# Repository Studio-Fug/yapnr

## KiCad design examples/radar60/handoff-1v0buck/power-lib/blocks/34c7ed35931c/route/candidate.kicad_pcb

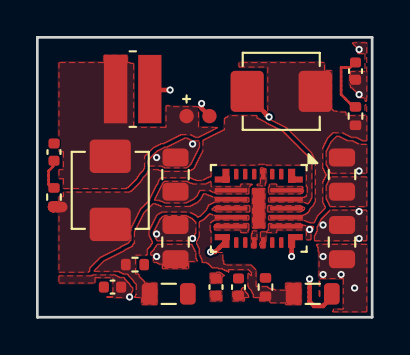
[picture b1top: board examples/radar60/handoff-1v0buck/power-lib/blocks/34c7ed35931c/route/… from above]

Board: 6 copper layers, 18.6 x 15.5 mm, 20 parts (0 on the bottom side), 15 nets.

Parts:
C14, C15, C16, C17: C_0805_2012Metric
C27, C28, C29, C30, C31: C_0402_1005Metric
L1, L2: L_0805_2012Metric
L3, L4: L_Vishay_IHLP-1616
R30, R31, R32, R33: R_0402_1005Metric
R_SH1: Vishay_WFCP0612_1632Metric
TP1: Radar60_KelvinSense_2Pad_P1.27mm
U2: TI_RNF0026C_VQFN-HR-26_4.5x4mm_P0.5mm

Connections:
1V0_BUCK: L3.2, R_SH1.1, TP1.1
1V0_SH: R_SH1.2, TP1.2
1V2_BUCK: L2.2, U2.14
1V8_BUCK: L4.2, U2.21
3V3: L1.2, U2.8
5V_SYS: C14.1, C15.1, C16.1, C17.1, C31.1, U2.9, U2.13, U2.18, U2.22, U2.26
GND: C14.2, C15.2, C16.2, C17.2, C27.2, C28.2, C29.2, C30.2, C31.2, U2.4, U2.11, U2.17, U2.24, U2.27
PMIC_SW_B0: L1.1, R30.1, U2.10
PMIC_SW_B1: L2.1, R31.1, U2.12
PMIC_SW_B2: L3.1, R32.1, U2.25
PMIC_SW_B3: L4.1, R33.1, U2.23
snb0: C27.1, R30.2
snb1: C28.1, R31.2
snb2: C29.1, R32.2
snb3: C30.1, R33.2

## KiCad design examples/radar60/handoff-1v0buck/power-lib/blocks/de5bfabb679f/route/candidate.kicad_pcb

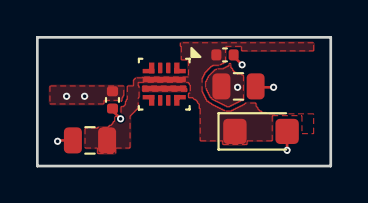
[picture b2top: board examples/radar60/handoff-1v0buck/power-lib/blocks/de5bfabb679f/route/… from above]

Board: 6 copper layers, 16.3 x 7.1 mm, 6 parts (0 on the bottom side), 3 nets.

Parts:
C33, C36: C_0805_2012Metric
C34, C37: C_0402_1005Metric
D3: D_SMF
U5: TI_RPW0010A_VQFN-HR-10_2x2mm_P0.45mm

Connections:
5V_SYS: C36.1, C37.1, U5.6
GND: C33.2, C34.2, C36.2, C37.2, D3.2, U5.8
VIN_5V: C33.1, C34.1, D3.1, U5.5

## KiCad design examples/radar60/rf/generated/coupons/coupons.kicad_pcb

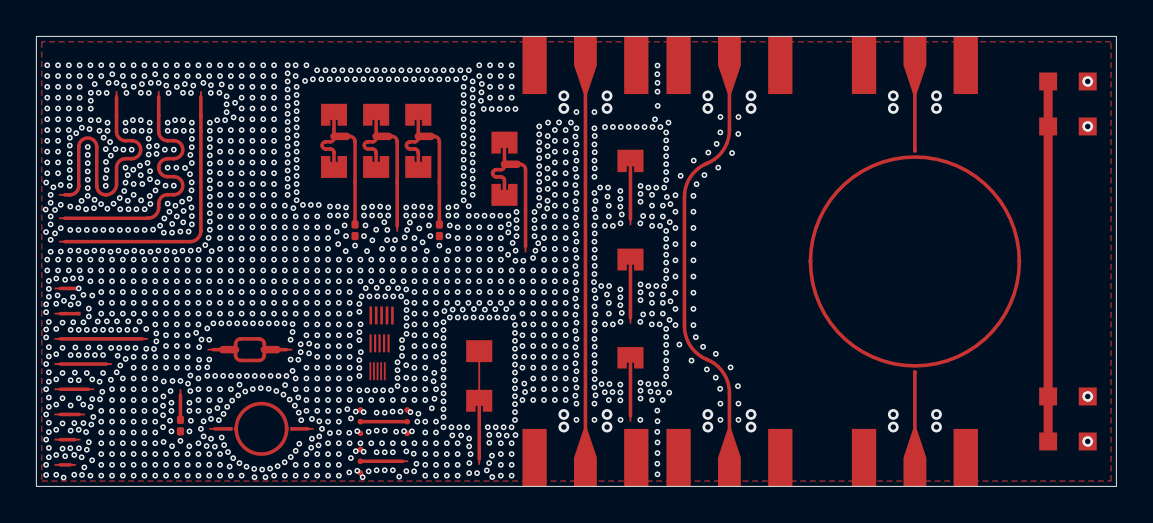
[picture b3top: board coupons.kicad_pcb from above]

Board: 6 copper layers, 60.0 x 25.0 mm, 97 parts (0 on the bottom side), 33 nets.

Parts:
CP0: cp60/0/a; CP_PAD
CP1: cp60/0/b; CP_PAD
CP2: cp60/1/a; CP_PAD
CP3: cp60/1/b; CP_PAD
CP4: cp60/2/a; CP_PAD
CP5: cp60/2/b; CP_PAD
CP6: cp60/3/a; CP_PAD
CP7: cp60/3/b; CP_PAD
CP8: cp60/4/a; CP_PAD
CP9: cp60/4/b; CP_PAD
CP10: cp60/5/a; CP_PAD
CP11: cp60/5/b; CP_PAD
CP12: cp60/open; CP_PAD
CP13: cp60/open/end; CP_PAD
CP14: cp60/short; CP_PAD
CP15: cpz; CP_PAD
CP16: ring60/anchor-1; CP_PAD
CP17: ring60/anchor1; CP_PAD
CP18: ring/a; CP_PAD
CP19: ring/a/end; CP_PAD
CP20: ring/b; CP_PAD
CP21: ring/b/end; CP_PAD
CP22: cpd/a; CP_PAD
CP23: cpd/b; CP_PAD
CP24: cpl1/land18.00; CP_PAD
CP25: cpl1/g18.00-1; CP_PAD
CP26: cpl1/g18.001; CP_PAD
CP27: cpl1/b; CP_PAD
CP28: cpl2/land18.00; CP_PAD
CP29: cpl2/g18.00-1; CP_PAD
CP30: cpl2/g18.001; CP_PAD
CP31: cpl2/land20.60; CP_PAD
CP32: cpl2/g20.60-1; CP_PAD
CP33: cpl2/g20.601; CP_PAD
CP34: cpm/0/0; CP_PAD
CP35: cpm/0/1; CP_PAD
CP36: cpm/0/2; CP_PAD
CP37: cpm/0/3; CP_PAD
CP38: cpm/0/4; CP_PAD
CP39: cpm/1/0; CP_PAD
CP40: cpm/1/1; CP_PAD
CP41: cpm/1/2; CP_PAD
CP42: cpm/1/3; CP_PAD
CP43: cpm/1/4; CP_PAD
CP44: cpm/2/0; CP_PAD
CP45: cpm/2/1; CP_PAD
CP46: cpm/2/2; CP_PAD
CP47: cpm/2/3; CP_PAD
CP48: cpm/2/4; CP_PAD
CP49: cpa/ser/lo; CP_PAD
CP50: cpa/ser/hi; CP_PAD
CP51: cpa/ser/link; CP_PAD
CP52: cpa/ser; CP_PAD
CP53: cpt/TX1/a; CP_PAD
CP54: cpt/TX1/b; CP_PAD
CP55: cpt/TX2/a; CP_PAD
CP56: cpt/TX2/b; CP_PAD
CP57: cpt/TX3/a; CP_PAD
CP58: cpt/TX3/b; CP_PAD
CP59: cpa/cell/0/0; CP_PAD
CP60: cpa/cell/0/1; CP_PAD
CP61: cpa/cell/1/0; CP_PAD
CP62: cpa/cell/1/1; CP_PAD
CP63: cpa/cell; CP_PAD
CP64: cpa/cell/2/0; CP_PAD
CP65: cpa/cell/2/1; CP_PAD
CP66: cpa/corp/0; CP_PAD
CP67: cpa/corp/1; CP_PAD
CP68: cpa/corp; CP_PAD
CP69, CP70: cpa/pM25; CP_PAD
CP71, CP72: cpa/pNOM; CP_PAD
CP73, CP74: cpa/pP25; CP_PAD
CP75: ring6/anchor-1; CP_PAD
CP76: ring6/anchor1; CP_PAD
CP77: ring6/A/end; CP_PAD
CP78: ring6/B/end; CP_PAD
CP79: bar0/0; CP_PAD
CP80: bar0/1; CP_PAD
CP81: bar0/2; CP_PAD
CP82: bar0/3; CP_PAD
CP83: bar1/0; CP_PAD
CP84: bar1/1; CP_PAD
CP85: bar1/2; CP_PAD
CP86: bar1/3; CP_PAD
J6RA, J6RB, J60A, J60B, J61A, J61B: SMA-J-P-H-ST-EM1; SMA_EdgeLaunch_SMA-J-P-H-ST-EM1
MO1: coupon mask opening; RFM1_MASK
RTA0, RTA2: 50R 0201 thin film; R_0201_0603Metric_LOAD
RTZ1: 50R 0201 thin film; R_0201_0603Metric_LOAD

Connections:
CP6_LINE: J61A.1, J61B.1
CP6_RING: CP75.1, CP76.1
CP6_RING_A: CP77.1, J6RA.1
CP6_RING_B: CP78.1, J6RB.1
CP6_R_L1: CP79.1, CP80.1, CP81.1, CP82.1
CP6_R_L3: CP83.1, CP84.1, CP85.1, CP86.1
CP6_THRU: J60A.1, J60B.1
CP60_L0: CP0.1, CP1.1
CP60_L1: CP2.1, CP3.1
CP60_L2: CP4.1, CP5.1
CP60_L3: CP6.1, CP7.1
CP60_L4: CP8.1, CP9.1
CP60_L5: CP10.1, CP11.1
CP60_OPEN: CP12.1, CP13.1
CP60_RING: CP16.1, CP17.1
CP60_RING_A: CP18.1, CP19.1
CP60_RING_B: CP20.1, CP21.1
CPA_CELL: CP61.1, CP62.1, CP63.1
CPA_CORP: CP66.1, CP67.1, CP68.1
CPA_D0: CP59.1, CP60.1, RTA0.1
CPA_D2: CP64.1, CP65.1, RTA2.1
CPA_PM25: CP69.1, CP70.1
CPA_PNOM: CP71.1, CP72.1
CPA_PP25: CP73.1, CP74.1
CPA_SER: CP49.1, CP50.1, CP51.1, CP52.1
CPD_CONV: CP22.1, CP23.1
CPL1: CP24.1, CP27.1
CPL2: CP28.1, CP31.1
CPT_TX1: CP53.1, CP54.1
CPT_TX2: CP55.1, CP56.1
CPT_TX3: CP57.1, CP58.1
CPZ_LOAD: CP15.1, RTZ1.1
GND: CP14.1, CP25.1, CP26.1, CP29.1, CP30.1, CP32.1, CP33.1, J6RA.2, J6RB.2, J60A.2, J60B.2, J61A.2, J61B.2, RTA0.2, RTA2.2, RTZ1.2

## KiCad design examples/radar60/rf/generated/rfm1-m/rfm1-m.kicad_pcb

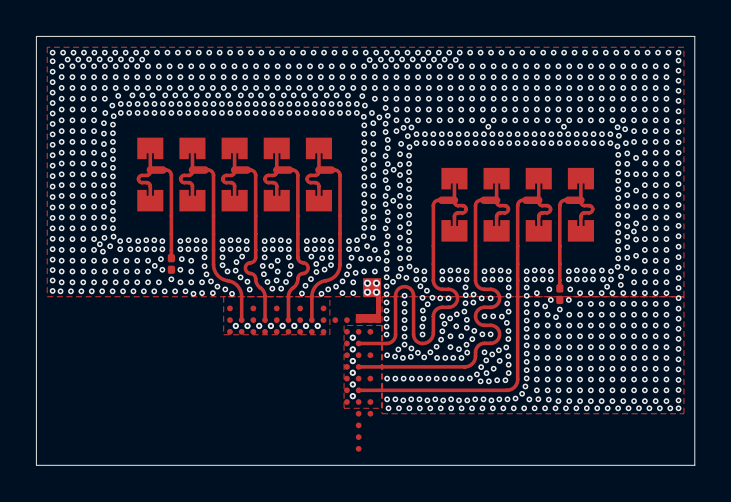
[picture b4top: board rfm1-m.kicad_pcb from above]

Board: 6 copper layers, 36.6 x 23.8 mm, 14 parts (0 on the bottom side), 11 nets.

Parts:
ANT_RX1, ANT_RX2, ANT_RX3, ANT_RX4: 2-patch corporate column; COL2_CORPORATE
ANT_RXD0: 2-patch corporate column, terminated dummy; COL2_DUMMY
ANT_TX1, ANT_TX2, ANT_TX3: 2-patch corporate column; COL2_CORPORATE
ANT_TXD4: 2-patch corporate column, terminated dummy; COL2_DUMMY
MO1: RF mask opening; RFM1_MASK
PA1: VOUT_PA feed (D14); RFM1_PA_FEED
RT1, RT2: 50R 0201 thin film; R_0201_0603Metric_LOAD
U1: IWR6843AQGABLR (rings 0-2 of the RF edges); IWR6843_ABL0161_RF_EDGES

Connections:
1V0_PA: PA1.1, U1.A2, U1.B2
GND: RT1.2, RT2.2, U1.A3, U1.A5, U1.A7, U1.A9, U1.B3, U1.B5, U1.B7, U1.B9, U1.C3, U1.C4, U1.C5, U1.C6, U1.C7, U1.C8, U1.C9, U1.E1, U1.E2, U1.E3, U1.F3, U1.G1, U1.G2, U1.G3, U1.H3, U1.J1, U1.J2, U1.J3, U1.K3, U1.L1, U1.L2, U1.L3, U1.M3, U1.N1, U1.N2, U1.N3
RX1: ANT_RX1.1, U1.M2
RX2: ANT_RX2.1, U1.K2
RX3: ANT_RX3.1, U1.H2
RX4: ANT_RX4.1, U1.F2
RXD0: ANT_RXD0.1, RT1.1
TX1: ANT_TX1.1, U1.B4
TX2: ANT_TX2.1, U1.B6
TX3: ANT_TX3.1, U1.B8
TXD4: ANT_TXD4.1, RT2.1
